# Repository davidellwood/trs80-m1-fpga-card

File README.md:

# TRS-80 Model I expansion system

All-through-hole hardware, FPGA design, firmware and Z80 software for the TRS-80 Model I.

- **Rev 2 (current):** three ECB Eurocard daughter cards, with two ways to connect them to the Model I. The design is in [docs/rev2-architecture.md](docs/rev2-architecture.md).
  - The custom **backplane**: 5 slots, 4 layers, with an Expansion Interface pass-through.
  - The **bridge card**: plugs into a standard ECB backplane. The Model I connects by ribbon to a right-angle header, and there's no EI.
- **Rev 0.1:** the original single card on a Tang Nano 9K. It remains here as a working reference; see [docs/hardware-design.md](docs/hardware-design.md).

*Rev 2 system on the custom backplane, raytraced from the KiCad designs by `hardware/tools/render_system.py`. The Tang Nano 20K and the SD breakout are simplified stand-in models.*

## Boards

All are routed, and DRC is clean against their schematics. None has been built yet.

| Board | Folder | What it does |
|---|---|---|
| **Bridge card** | `hardware/card-bridge/` | Option 2, instead of the backplane: Model I → ECB bridge on a 100 × 160 Eurocard for a standard ECB backplane (e.g. RetroBrew). The Model I bus arrives on a right-angle 2 × 20 header. Buffered A0–A15, hysteresis receivers on the strobes and a claim-decoded data buffer for a longer cable, and a GAL rebuilding MREQ*/IORQ*/RD*/WR*/M1*/RESET*. No Expansion Interface |
| **Backplane** | `hardware/backplane/` | Option 1: Model I → ECB bridge, 5 DIN 41612 C96 slots (RetroBrew ECB pinout), 4 layers. A GAL rebuilds MREQ*/IORQ*/RD*/WR*/M1* from the Model I strobes. It passes the bus through to the Expansion Interface; JP8/JP9 choose direct or GAL-gated EI RD*/WR* |
| **FPGA card** | `hardware/card-fpga/` | Tang Nano 20K + IDT7132 2 KB dual-port RAM at 3000h. A hardware sprite engine on ports 52h/53h draws into a 1 KB frame buffer the Z80 copies to the screen with LDIR, and an Am9511 maths coprocessor sits on ports 50h/51h |
| **SD card** | `hardware/card-sd/`, `firmware/sdcard/` | Raspberry Pi Pico running a FreHD-compatible hard disk on ports C0h–CFh: `.HDV` images, read-only DMK/JV3/JV1 floppy images, file transfer, and a DS1307 real-time clock |
| **Banked memory** | `hardware/card-xmem/` | 512 KB SRAM paged into 8000h–FFFFh, software-compatible with X-MEM/80 (OUT 41h/42h, 16 KB pages) and SuperMem (OUT 43h, 32 KB pages) |

**System map**
- **Memory:** 3000h–37DFh is the FPGA card's shared RAM; 8000h–FFFFh is banked RAM.
- **I/O:** 41h–43h banked memory, 50h–53h FPGA card, C0h–CFh SD card.
- **ECB line c10** is EXTMEM*. The banked-memory card drives it so the backplane can hide an Expansion Interface's own RAM. The bridge card, which has no EI, just pulls it up.

## Repository layout

| Path | Contents |
|---|---|
| `docs/rev2-architecture.md` | Rev 2 design: ECB pinout, bridge, each card as built, checks before ordering |
| `docs/bridge-card-timing.md` | How the bridge rebuilds the ECB signals the Model I bus lacks (MREQ*, IORQ*, M1*…), with timing diagrams |
| `docs/hardware-design.md` | Rev 0.1 card: memory and I/O maps, Tang Nano 9K pinout, BOM |
| `docs/sprite-engine.md`, `docs/am9511.md` | Sprite engine port protocol; Am9511 core programming model and accuracy |
| `hardware/gal/` | CUPL sources for all GALs: rev 0.1 decoders, `ecb_bridge` (backplane), `ecb_mem_decode`/`ecb_io_decode` (FPGA card), `ecb_sd_decode` (SD card), `ecb_xmem_io`/`ecb_xmem_mem` (banked memory). Compiled JEDEC files, verified by fuse-level simulation, are in `galasm/`; see [hardware/gal/README.md](hardware/gal/README.md) |
| `hardware/tools/` | Python generators that bootstrap each KiCad project: `gen_*.py` for schematics, `gen_*_pcb.py` for boards. Shared helpers are `kicadgen.py`, `pcbgen.py`, `ecb.py` and `parts.py`; `pcb_fixup.py` does post-route DRC clean-up. **Don't re-run a generator once its board is routed or edited in KiCad.** |
| `hardware/kicad/` | Rev 0.1 KiCad project (routed, DRC clean) |
| `fpga/` | Gowin Verilog: bus logic, sprite engine, Am9511 core. `build.tcl` builds for the Tang Nano 9K and `build20k.tcl` for the 20K; `sim/` holds the testbenches. See [fpga/README.md](fpga/README.md) |
| `firmware/sdcard/` | Pico firmware for the SD card (Pico SDK 2.3.1 + FatFs R0.15). Build with `build.ps1`; host tests are in `test/`. See [firmware/sdcard/README.md](firmware/sdcard/README.md) |
| `software/` | Z80 library, assembly demo (DEMO/CMD), Level II BASIC USR module and demo, emulator-based tests. See [software/README.md](software/README.md) |

## Status

| Part | Status |
|---|---|
| FPGA (20K) | 33% logic, Fmax 58 MHz; all simulation suites pass |
| SD firmware | Builds warning-free (64 KB); 79 host-side protocol checks pass |
| Z80 software | Tested in the project's Z80 emulator against the card models |

**Not done yet:**
- **Hardware:** nothing has been tried on real hardware. GAL JEDEC files are compiled and verified (`hardware/gal/galasm/`). Gerbers and drill files for all four boards are ready: see [hardware/ORDERING.md](hardware/ORDERING.md).
- **Checks before ordering:**
  - Tang Nano 20K row spacing and orientation.
  - The IDT7132 and AS6C4008 pinouts.
  - The SD module's pin order.
  - Whether the Model I accepts read data at 3000h.
  - Bus timing on the first boards.

  The full lists are in each section of [docs/rev2-architecture.md](docs/rev2-architecture.md).

## Licence

- **Software, FPGA HDL, firmware and tools:** MIT ([LICENSE](LICENSE)).
- **Hardware designs** (everything under `hardware/`: KiCad projects, GAL sources and JEDEC files, Gerbers): CERN Open Hardware Licence v2 – Permissive ([hardware/LICENSE](hardware/LICENSE)).
- **Third-party code:** `firmware/sdcard/lib/fatfs` is ChaN's FatFs under its own licence ([lib/fatfs/LICENSE.txt](firmware/sdcard/lib/fatfs/LICENSE.txt)).

## Credits

- The bus-interface ideas and card-edge geometry come from TRS-IO M1 v1.3-xray (Arno Puder).
- The Am9511 behavioural reference is ratboy666/am9511 (MIT).
- The ECB pinout follows the RetroBrew ECB backplane.
- The SD card and banked-memory card are independent implementations of the published FreHD (fvecoven/FreHDv1) and X-MEM/80 (lambdamikel/x-mem-80) interfaces. Both projects are GPL-3.0; no code or circuits were copied.

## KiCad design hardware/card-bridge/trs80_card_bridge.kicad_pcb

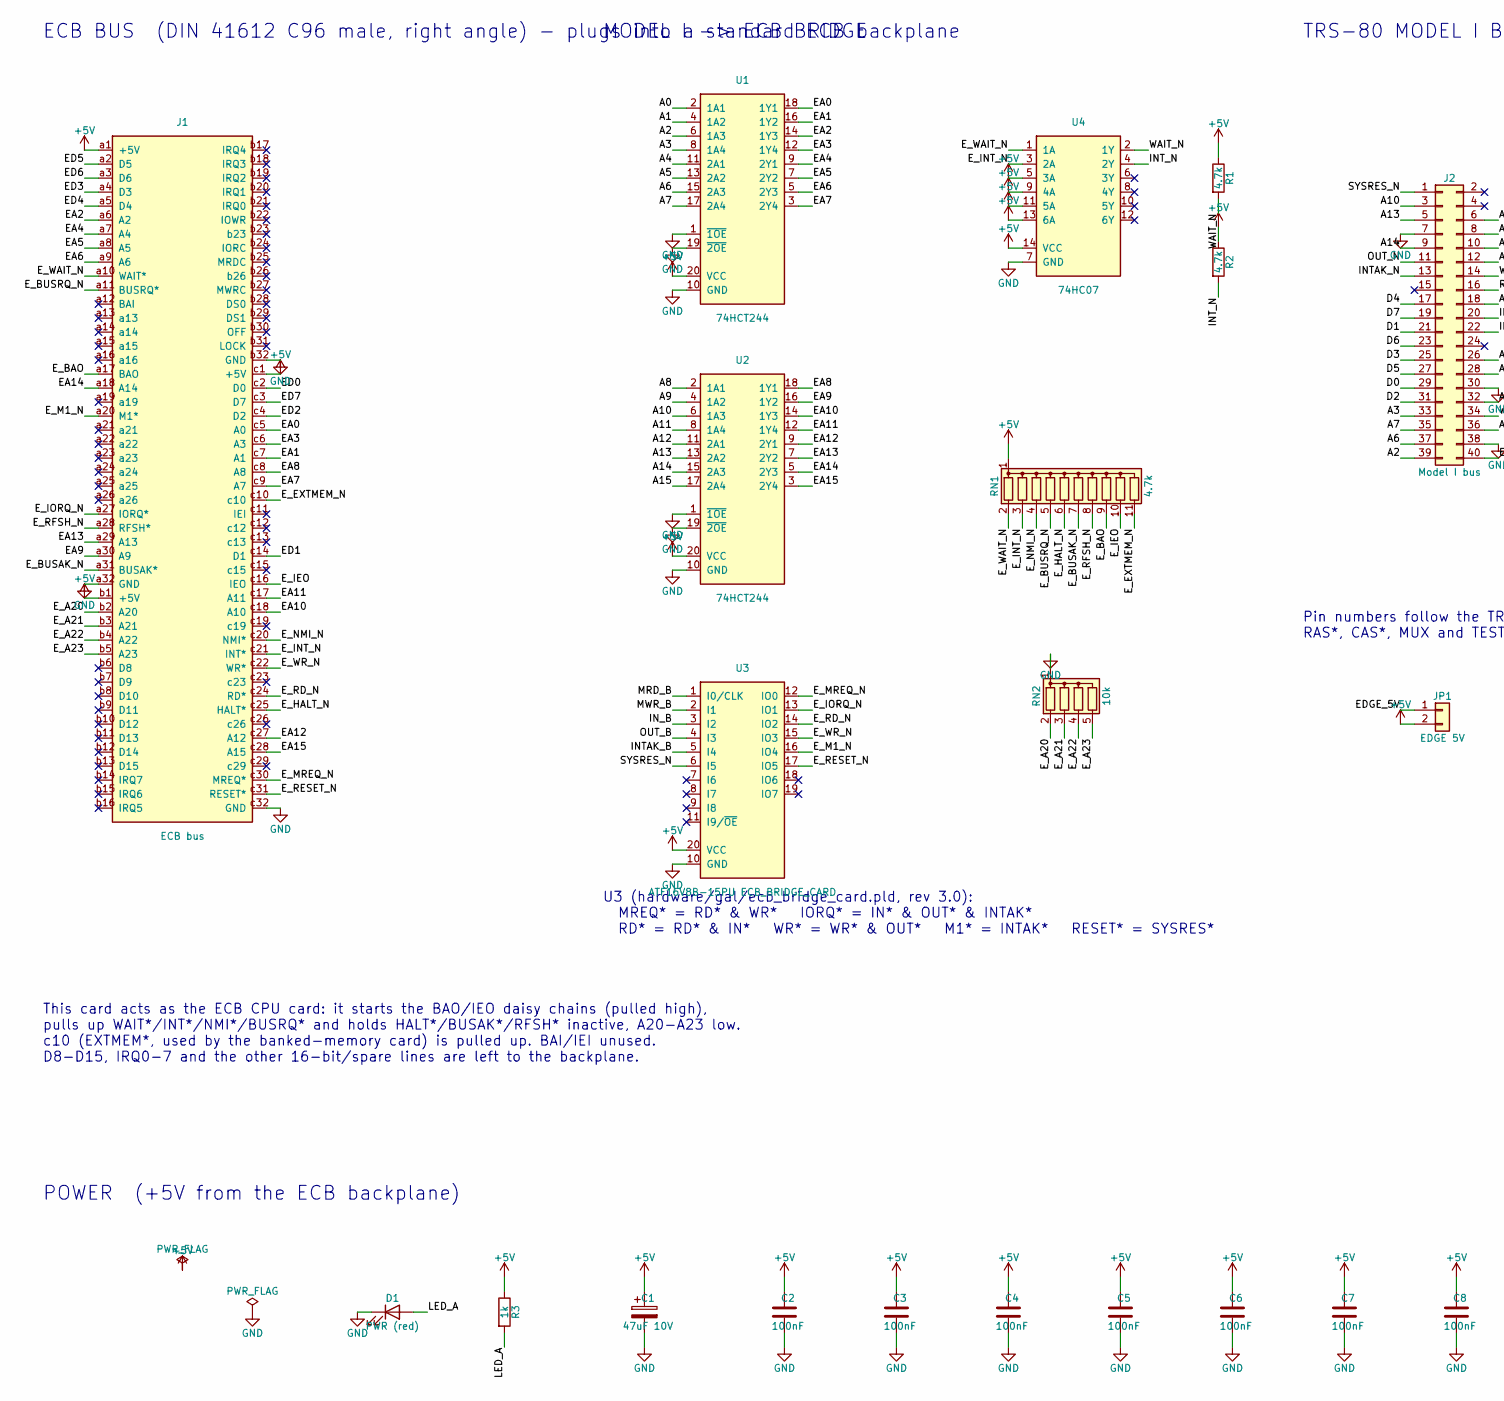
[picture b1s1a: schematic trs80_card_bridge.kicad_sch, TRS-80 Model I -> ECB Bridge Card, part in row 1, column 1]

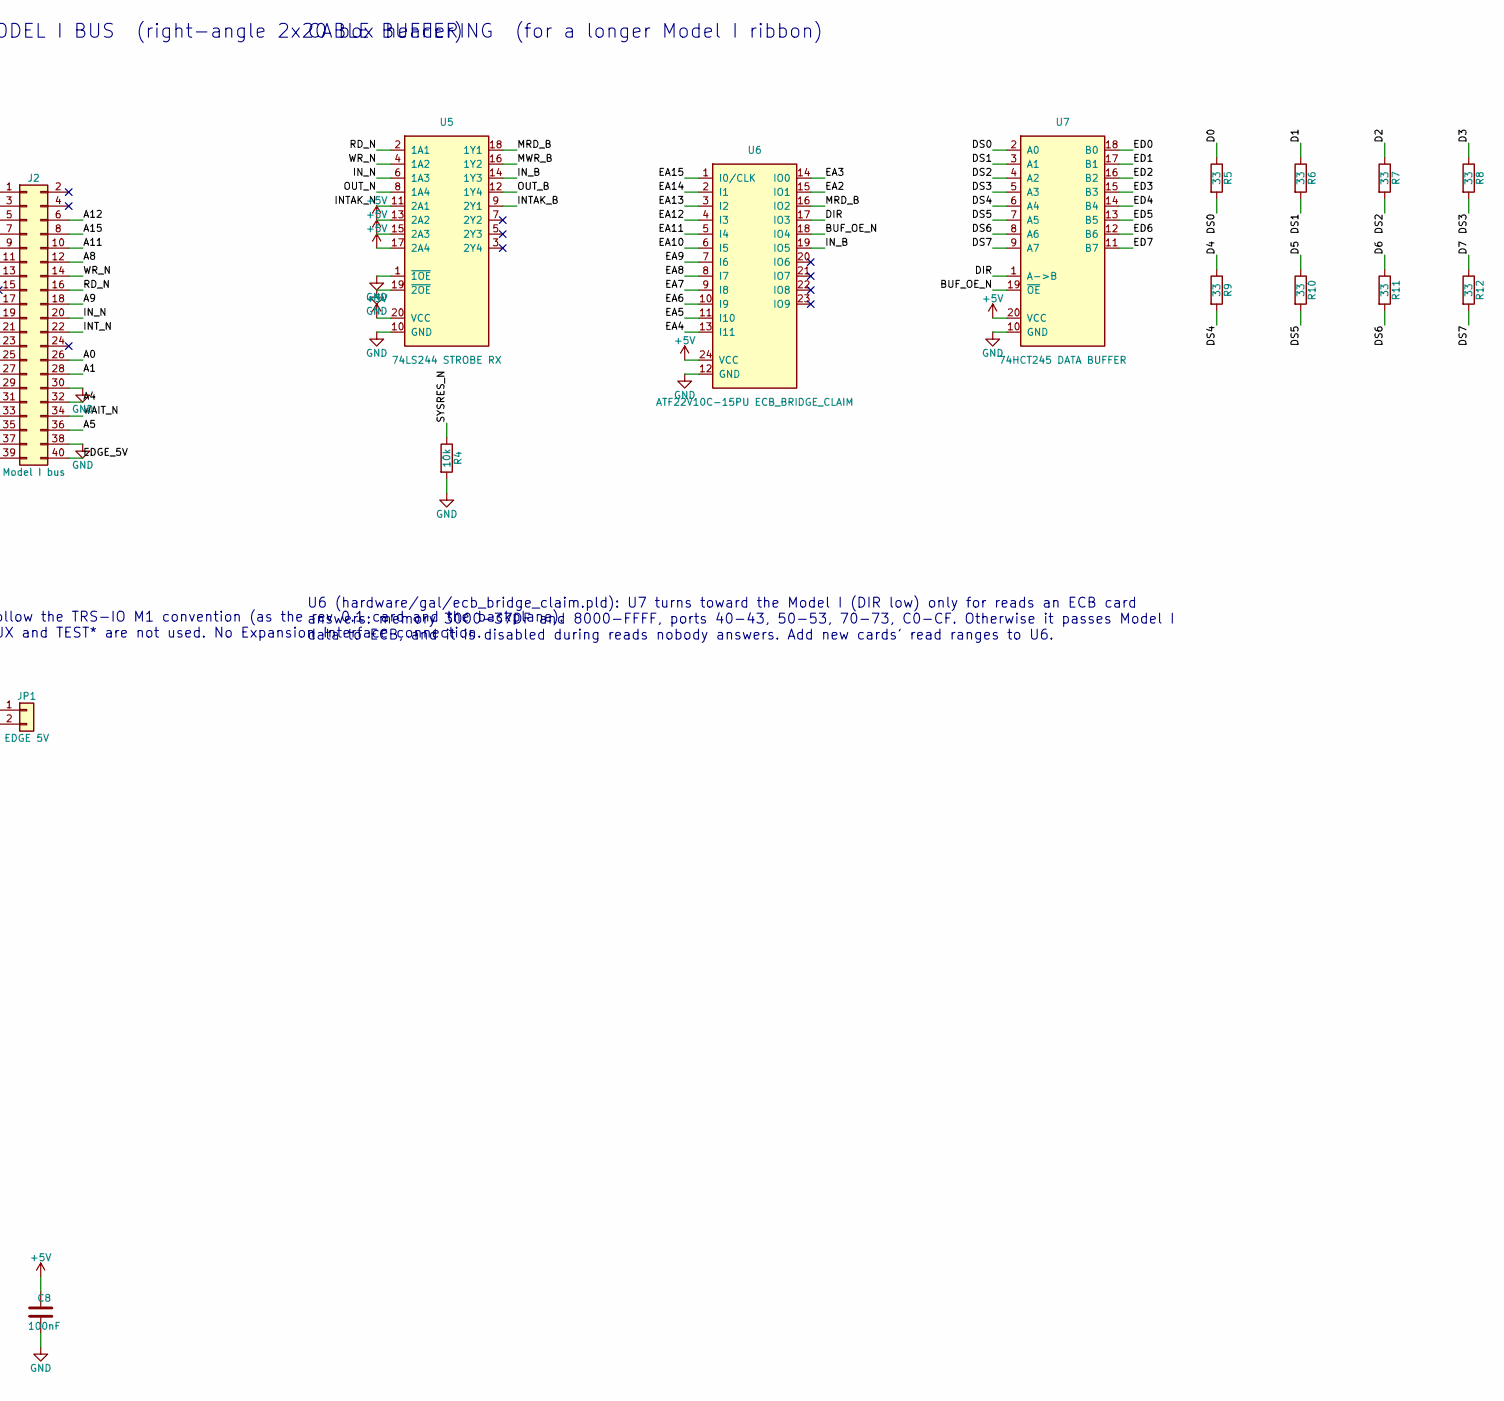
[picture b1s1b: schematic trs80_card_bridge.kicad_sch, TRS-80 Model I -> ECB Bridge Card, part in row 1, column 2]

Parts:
C1: 47uF 10V; CP_Radial_D6.3mm_P2.50mm
C2, C3, C4, C5, C6, C7, C8: 100nF; C_Disc_D5.0mm_W2.5mm_P5.00mm
D1: PWR (red); LED_D3.0mm
J1: ECB bus; DIN41612_C_3x32_Male_Horizontal_THT
J2: Model I bus; IDC-Header_2x20_P2.54mm_Horizontal
JP1: EDGE 5V; PinHeader_1x02_P2.54mm_Vertical
R1, R2: 4.7k; R_Axial_DIN0207_L6.3mm_D2.5mm_P10.16mm_Horizontal
R3: 1k; R_Axial_DIN0207_L6.3mm_D2.5mm_P10.16mm_Horizontal
R4: 10k; R_Axial_DIN0207_L6.3mm_D2.5mm_P10.16mm_Horizontal
R5, R6, R7, R8, R9, R10, R11, R12: 33; R_Axial_DIN0207_L6.3mm_D2.5mm_P10.16mm_Horizontal
RN1: 4.7k; R_Array_SIP11
RN2: 10k; R_Array_SIP5
U1, U2: 74HCT244; DIP-20_W7.62mm
U3: ATF16V8B-15PU ECB_BRIDGE_CARD; DIP-20_W7.62mm_Socket
U4: 74HC07; DIP-14_W7.62mm
U5: 74LS244 STROBE RX; DIP-20_W7.62mm
U6: ATF22V10C-15PU ECB_BRIDGE_CLAIM; DIP-24_W7.62mm_Socket
U7: 74HCT245 DATA BUFFER; DIP-20_W7.62mm

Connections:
+5V: C1.1, C2.1, C3.1, C4.1, C5.1, C6.1, C7.1, C8.1, J1.a1 (+5V), J1.b1 (+5V), J1.c1 (+5V), JP1.2, R1.1, R2.1, R3.1, RN1.1 (common), U1.20 (VCC), U2.20 (VCC), U3.20 (VCC), U4.5 (3A), U4.9 (4A), U4.11 (5A), U4.13 (6A), U4.14 (VCC), U5.13 (2A2), U5.15 (2A3), U5.17 (2A4), U5.20 (VCC), U6.24 (VCC), U7.20 (VCC)
/A0: J2.26, U1.2 (1A1)
/A1: J2.28, U1.4 (1A2)
/A2: J2.39, U1.6 (1A3)
/A3: J2.33, U1.8 (1A4)
/A4: J2.32, U1.11 (2A1)
/A5: J2.36, U1.13 (2A2)
/A6: J2.37, U1.15 (2A3)
/A7: J2.35, U1.17 (2A4)
/A8: J2.12, U2.2 (1A1)
/A9: J2.18, U2.4 (1A2)
/A10: J2.3, U2.6 (1A3)
/A11: J2.10, U2.8 (1A4)
/A12: J2.6, U2.11 (2A1)
/A13: J2.5, U2.13 (2A2)
/A14: J2.9, U2.15 (2A3)
/A15: J2.8, U2.17 (2A4)
/BUF_OE_N: U6.18 (IO4), U7.19 (~OE)
/D0: J2.29, R5.1
/D1: J2.21, R6.1
/D2: J2.31, R7.1
/D3: J2.25, R8.1
/D4: J2.17, R9.1
/D5: J2.27, R10.1
/D6: J2.23, R11.1
/D7: J2.19, R12.1
/DIR: U6.17 (IO3), U7.1 (A->B)
/DS0: R5.2, U7.2 (A0)
/DS1: R6.2, U7.3 (A1)
/DS2: R7.2, U7.4 (A2)
/DS3: R8.2, U7.5 (A3)
/DS4: R9.2, U7.6 (A4)
/DS5: R10.2, U7.7 (A5)
/DS6: R11.2, U7.8 (A6)
/DS7: R12.2, U7.9 (A7)
/EA0: J1.c5 (A0), U1.18 (1Y1)
/EA1: J1.c7 (A1), U1.16 (1Y2)
/EA2: J1.a6 (A2), U1.14 (1Y3), U6.15 (IO1)
/EA3: J1.c6 (A3), U1.12 (1Y4), U6.14 (IO0)
/EA4: J1.a7 (A4), U1.9 (2Y1), U6.13 (I11)
/EA5: J1.a8 (A5), U1.7 (2Y2), U6.11 (I10)
/EA6: J1.a9 (A6), U1.5 (2Y3), U6.10 (I9)
/EA7: J1.c9 (A7), U1.3 (2Y4), U6.9 (I8)
/EA8: J1.c8 (A8), U2.18 (1Y1), U6.8 (I7)
/EA9: J1.a30 (A9), U2.16 (1Y2), U6.7 (I6)
/EA10: J1.c18 (A10), U2.14 (1Y3), U6.6 (I5)
/EA11: J1.c17 (A11), U2.12 (1Y4), U6.5 (I4)
/EA12: J1.c27 (A12), U2.9 (2Y1), U6.4 (I3)
/EA13: J1.a29 (A13), U2.7 (2Y2), U6.3 (I2)
/EA14: J1.a18 (A14), U2.5 (2Y3), U6.2 (I1)
/EA15: J1.c28 (A15), U2.3 (2Y4), U6.1 (I0/CLK)
/ED0: J1.c2 (D0), U7.18 (B0)
/ED1: J1.c14 (D1), U7.17 (B1)
/ED2: J1.c4 (D2), U7.16 (B2)
/ED3: J1.a4 (D3), U7.15 (B3)
/ED4: J1.a5 (D4), U7.14 (B4)
/ED5: J1.a2 (D5), U7.13 (B5)
/ED6: J1.a3 (D6), U7.12 (B6)
/ED7: J1.c3 (D7), U7.11 (B7)
/EDGE_5V: J2.40, JP1.1
/E_A20: J1.b2 (A20), RN2.2 (R1)
/E_A21: J1.b3 (A21), RN2.3 (R2)
/E_A22: J1.b4 (A22), RN2.4 (R3)
/E_A23: J1.b5 (A23), RN2.5 (R4)
/E_BAO: J1.a17 (BAO), RN1.9 (R8)
/E_BUSAK_N: J1.a31 (BUSAK*), RN1.7 (R6)
/E_BUSRQ_N: J1.a11 (BUSRQ*), RN1.5 (R4)
/E_EXTMEM_N: J1.c10, RN1.11 (R10)
/E_HALT_N: J1.c25 (HALT*), RN1.6 (R5)
/E_IEO: J1.c16 (IEO), RN1.10 (R9)
/E_INT_N: J1.c21 (INT*), RN1.3 (R2), U4.3 (2A)
/E_IORQ_N: J1.a27 (IORQ*), U3.13 (IO1)
/E_M1_N: J1.a20 (M1*), U3.16 (IO4)
/E_MREQ_N: J1.c30 (MREQ*), U3.12 (IO0)
/E_NMI_N: J1.c20 (NMI*), RN1.4 (R3)
/E_RD_N: J1.c24 (RD*), U3.14 (IO2)
/E_RESET_N: J1.c31 (RESET*), U3.17 (IO5)
/E_RFSH_N: J1.a28 (RFSH*), RN1.8 (R7)
/E_WAIT_N: J1.a10 (WAIT*), RN1.2 (R1), U4.1 (1A)
/E_WR_N: J1.c22 (WR*), U3.15 (IO3)
/INTAK_B: U3.5 (I4), U5.9 (2Y1)
/INTAK_N: J2.13, U5.11 (2A1)
/INT_N: J2.22, R2.2, U4.4 (2Y)
/IN_B: U3.3 (I2), U5.14 (1Y3), U6.19 (IO5)
/IN_N: J2.20, U5.6 (1A3)
/LED_A: D1.2 (A), R3.2
/MRD_B: U3.1 (I0/CLK), U5.18 (1Y1), U6.16 (IO2)
/MWR_B: U3.2 (I1), U5.16 (1Y2)
/OUT_B: U3.4 (I3), U5.12 (1Y4)
/OUT_N: J2.11, U5.8 (1A4)
/RD_N: J2.16, U5.2 (1A1)
/SYSRES_N: J2.1, R4.1, U3.6 (I5)
/WAIT_N: J2.34, R1.2, U4.2 (1Y)
/WR_N: J2.14, U5.4 (1A2)
GND: C1.2, C2.2, C3.2, C4.2, C5.2, C6.2, C7.2, C8.2, D1.1 (K), J1.a32 (GND), J1.b32 (GND), J1.c32 (GND), J2.7, J2.30, J2.38, R4.2, RN2.1 (common), U1.1 (~1OE), U1.10 (GND), U1.19 (~2OE), U2.1 (~1OE), U2.10 (GND), U2.19 (~2OE), U3.10 (GND), U4.7 (GND), U5.1 (~1OE), U5.10 (GND), U5.19 (~2OE), U6.12 (GND), U7.10 (GND)

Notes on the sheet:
ECB BUS (DIN 41612 C96 male, right angle) - plugs into a standard ECB backplane
This card acts as the ECB CPU card: it starts the BAO/IEO daisy chains (pulled high), pulls up WAIT*/INT*/NMI*/BUSRQ* and holds HALT*/BUSAK*/RFSH* inactive, A20-A23 low. c10 (EXTMEM*, used by the banked-memory card) is pulled up. BAI/IEI unused. D8-D15, IRQ0-7 and the other 16-bit/spare lines are l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
TRS-80 MODEL I BUS (right-angle 2x20 box header)
Pin numbers follow the TRS-IO M1 convention (as the rev 0.1 card and the backplane). RAS*, CAS*, MUX and TEST* are not used. No Expansion Interface connection.
MODEL I -> ECB BRIDGE
U3 (hardware/gal/ecb_bridge_card.pld, rev 3.0): MREQ* = RD* & WR* IORQ* = IN* & OUT* & INTAK* RD* = RD* & IN* WR* = WR* & OUT* M1* = INTAK* RESET* = SYSRES*
CABLE BUFFERING (for a longer Model I ribbon)
U6 (hardware/gal/ecb_bridge_claim.pld): U7 turns toward the Model I (DIR low) only for reads an ECB card answers: memory 3000-37DF and 8000-FFFF, ports 40-43, 50-53, 70-73, C0-CF. Otherwise it passes Model I data to ECB, and it is disabled during reads nobody answers. Add new cards' read ranges to 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
POWER (+5V from the ECB backplane)

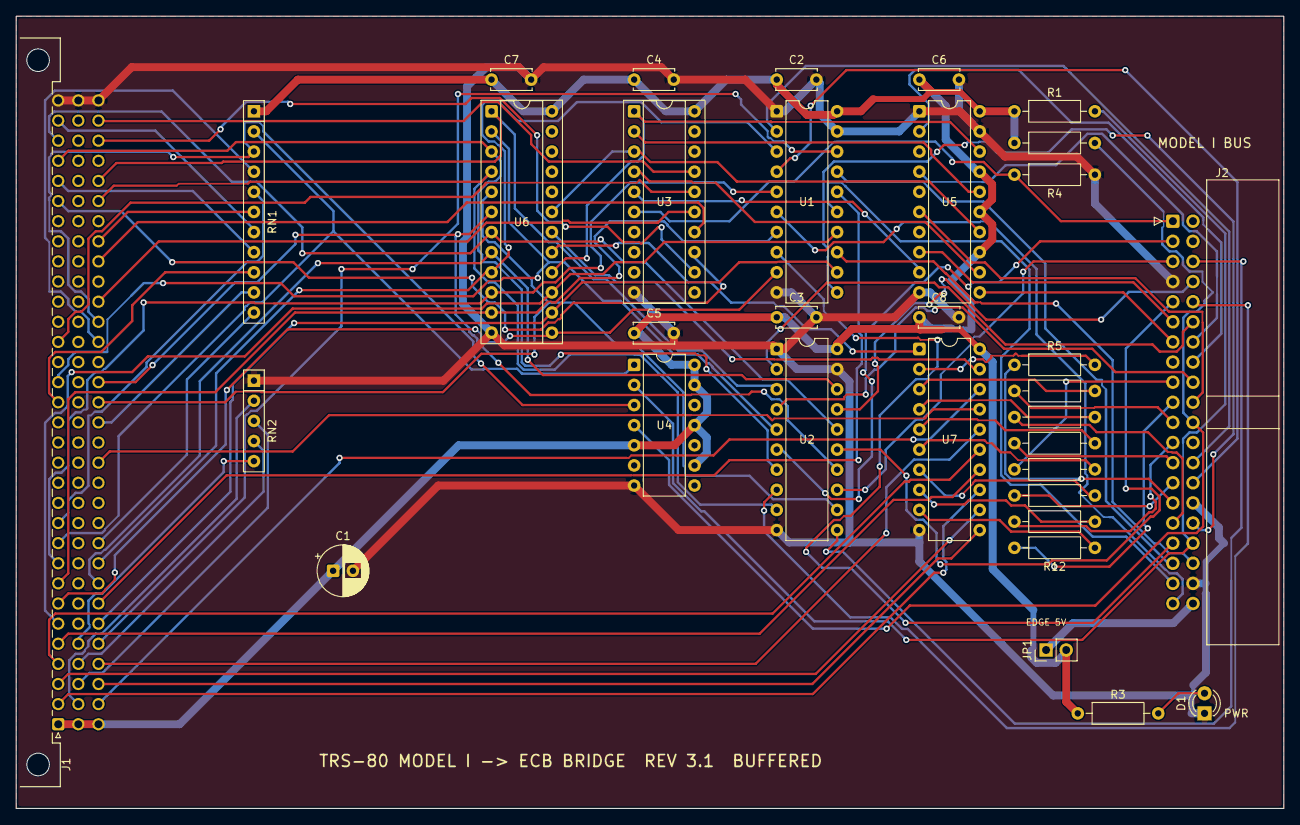
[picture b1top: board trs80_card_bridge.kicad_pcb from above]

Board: 2 copper layers, 160.0 x 100.0 mm, 33 parts (0 on the bottom side), 95 nets.
